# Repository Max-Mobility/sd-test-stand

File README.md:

# sd-test-stand
Test stand display, control, measurement, and validation code.

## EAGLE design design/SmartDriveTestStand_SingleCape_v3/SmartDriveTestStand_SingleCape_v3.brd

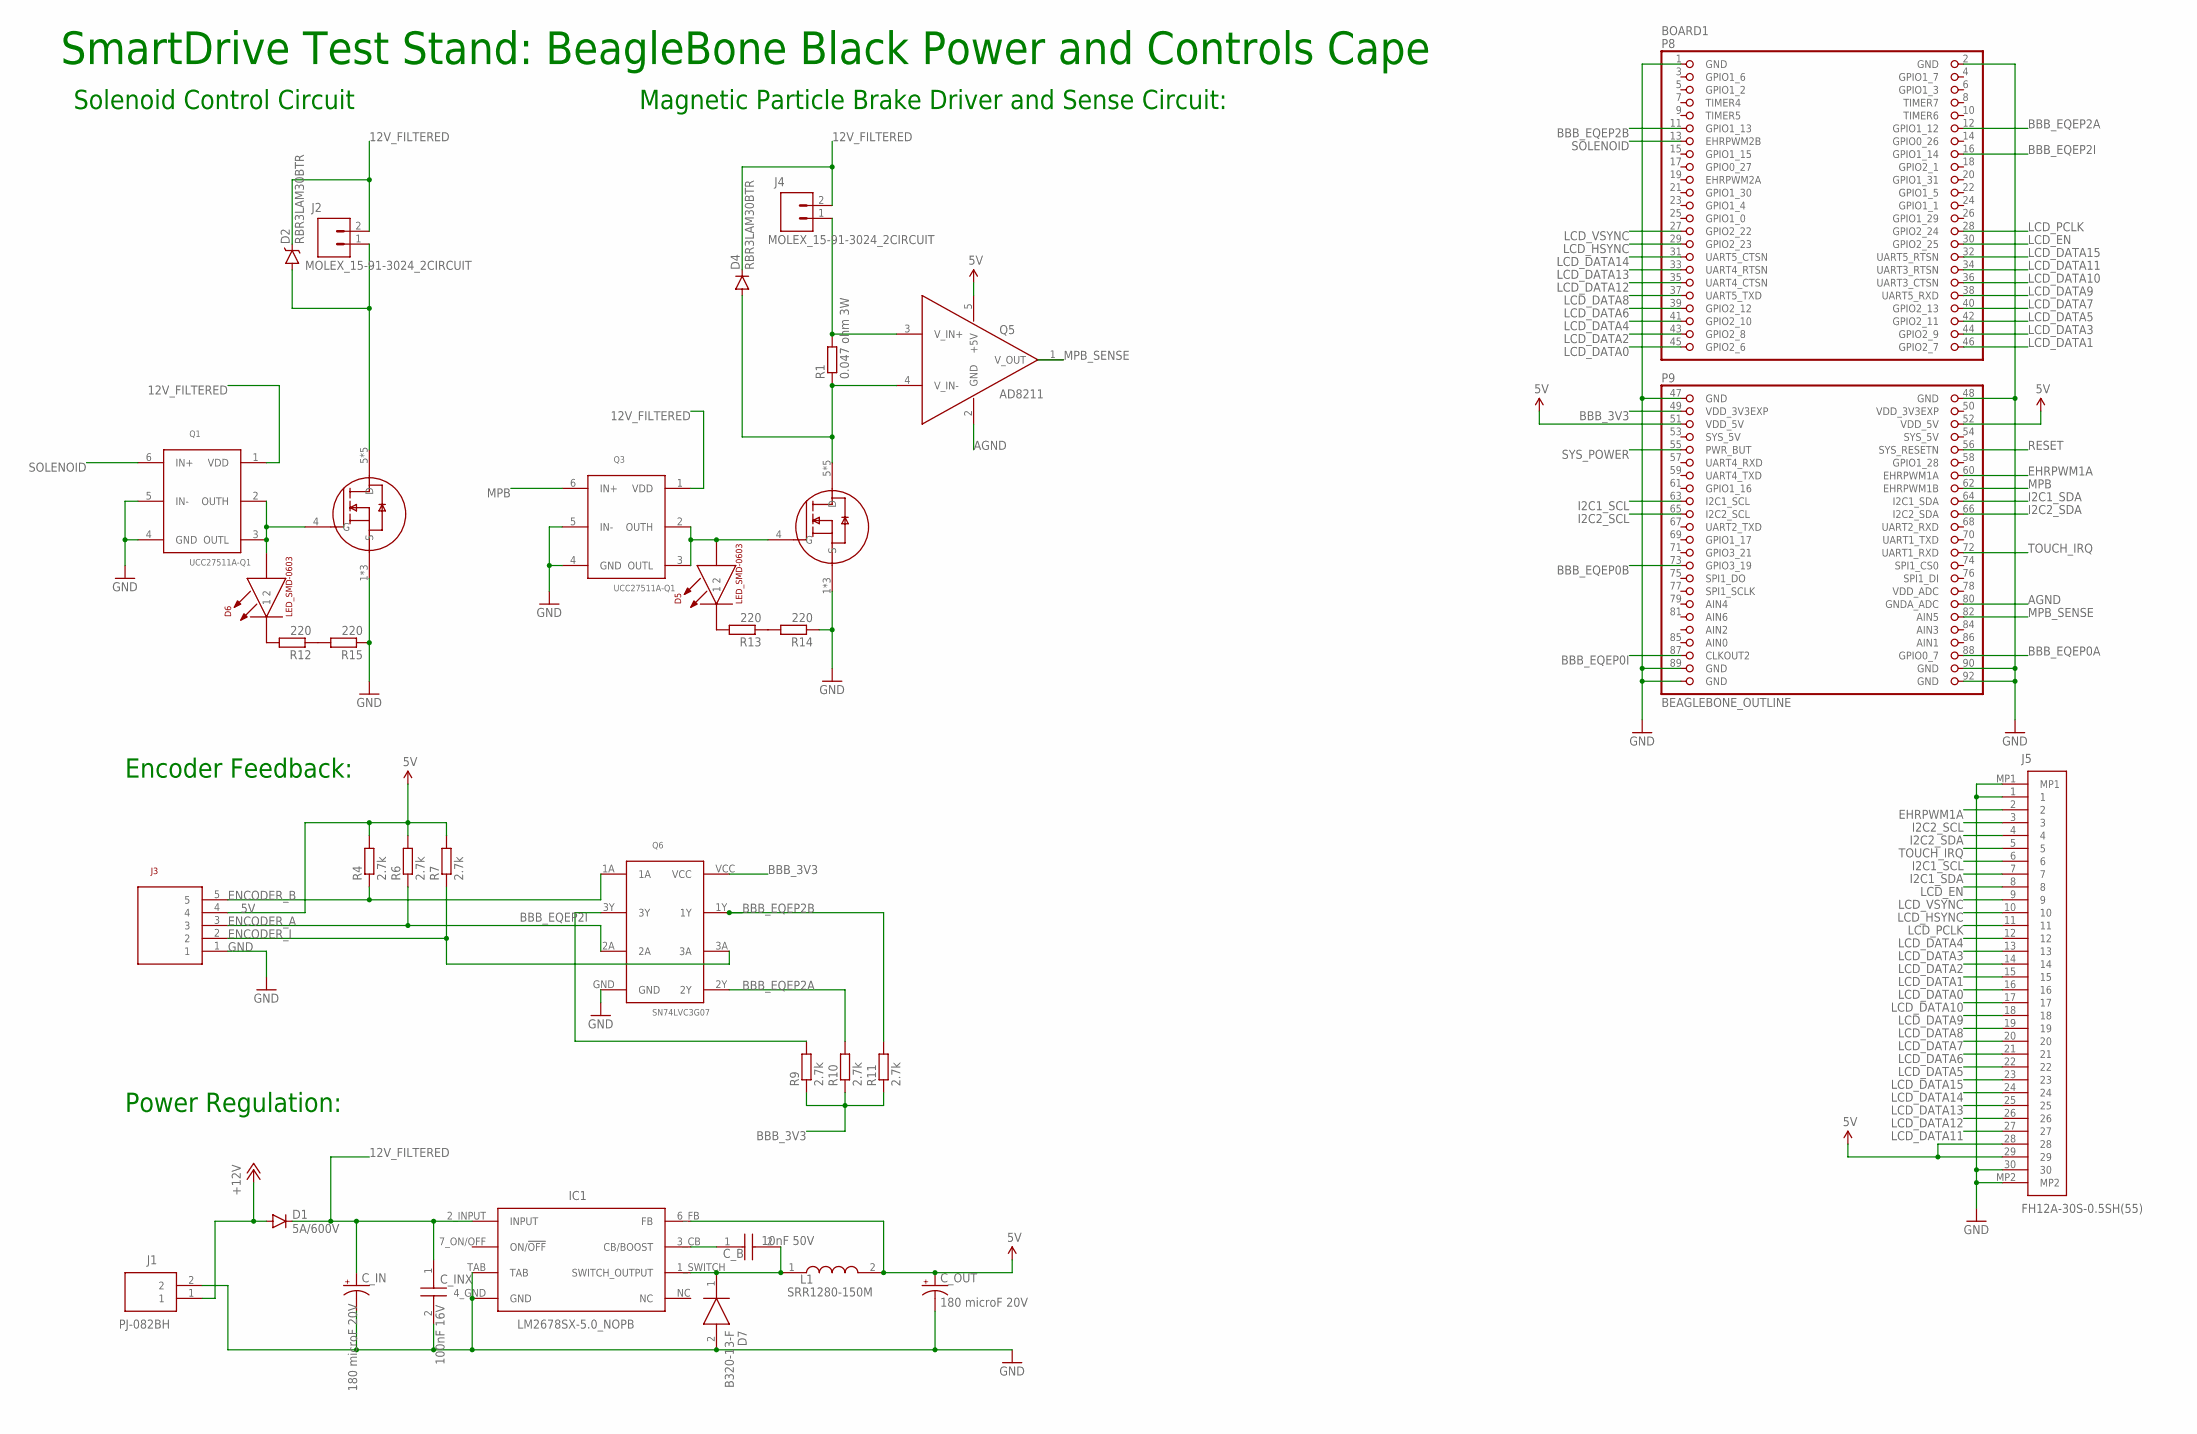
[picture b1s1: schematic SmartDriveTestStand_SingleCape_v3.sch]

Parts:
BOARD1: BEAGLEBONE_OUTLINE; BEAGLEBONE_SHIELD
C_B: 10nF 50V; CAPC2012X75N
C_IN: 180 microF 20V; CAPAE1030X800N
C_INX: 100nF 16V; CAPC1608X90N
C_OUT: 180 microF 20V; CAPAE1030X800N
D1: 5A/600V; SMC
D2, D4: RBR3LAM30BTR; SMA-DIODE
D5, D6: LED_SMD-0603; 0603_LED
D7: B320-13-F; DIOM7959X250N
IC1: LM2678SX-5.0_NOPB; KTW0007B
J1: PJ-082BH
J2, J4: MOLEX_15-91-3024_2CIRCUIT; MOLEX15-91-3024_2CIRCUIT
J3: MOLEX_15-91-3053_5CIRCUIT; MOLEX15-91-3053-5CIRCUIT
J5: FH12A-30S-0.5SH(55); FH12A30S05SH55
L1: SRR1280-150M
Q1, Q3: UCC27511A-Q1; SOT23-6
Q2, Q4: MOSFET_NCHANNELTI_CSD18533Q5A; SON_5X6MM_NEXFET
Q5: AD8211; SOT23-5
Q6: SN74LVC3G07
R1: 0.047 ohm 3W; RESISTOR-2512
R4, R6, R7, R9, R10, R11: 2.7k; RESISTOR-0603
R12, R13, R14, R15: 220; RESISTOR-0603

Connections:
5V: BOARD1.51 (VDD_5V), BOARD1.52 (VDD_5V), C_OUT.1 (+), IC1.6_FB (FB), J3.4, J5.28, J5.29, L1.2, Q5.5 (+5V), R4.P$2 (2), R6.P$2 (2), R7.P$2 (2)
12V_FILTERED: C_IN.1 (+), C_INX.1, D1.C, D2.C, D4.C, IC1.2_INPUT (INPUT), J2.2, J4.2, Q1.1 (VDD), Q3.1 (VDD)
+12V: D1.A, J1.1
AGND: BOARD1.80 (GNDA_ADC), Q5.2 (GND)
AIN0: BOARD1.85 (AIN0)
BBB_3V3: BOARD1.49 (VDD_3V3EXP), Q6.VCC, R9.P$1 (1), R10.P$1 (1), R11.P$1 (1)
BBB_EQEP0A: BOARD1.88 (GPIO0_7)
BBB_EQEP0B: BOARD1.73 (GPIO3_19)
BBB_EQEP0I: BOARD1.87 (CLKOUT2)
BBB_EQEP2A: BOARD1.12 (GPIO1_12), Q6.2Y, R10.P$2 (2)
BBB_EQEP2B: BOARD1.11 (GPIO1_13), Q6.1Y, R11.P$2 (2)
BBB_EQEP2I: BOARD1.16 (GPIO1_14), Q6.3Y, R9.P$2 (2)
EHRPWM1A: BOARD1.60 (EHRPWM1A), J5.2
ENCODER_A: J3.3, Q6.2A, R6.P$1 (1)
ENCODER_B: J3.5, Q6.1A, R4.P$1 (1)
ENCODER_I: J3.2, Q6.3A, R7.P$1 (1)
GND: BOARD1.1 (GND), BOARD1.2 (GND), BOARD1.47 (GND), BOARD1.48 (GND), BOARD1.89 (GND), BOARD1.90 (GND), BOARD1.91 (GND), BOARD1.92 (GND), C_IN.2 (-), C_INX.2, C_OUT.2 (-), D7.2 (A), IC1.4_GND (GND), IC1.TAB, J1.2, J3.1, J5.1, J5.30, J5.MP1, J5.MP2, Q1.4 (GND), Q1.5 (IN-), Q2.1 (S), Q2.2 (S), Q2.3 (S), Q3.4 (GND), Q3.5 (IN-), Q4.1 (S), Q4.2 (S), Q4.3 (S), Q6.GND, R14.P$1 (1), R15.P$1 (1)
I2C1_SCL: BOARD1.63 (I2C1_SCL), J5.6
I2C1_SDA: BOARD1.64 (I2C1_SDA), J5.7
I2C2_SCL: BOARD1.65 (I2C2_SCL), J5.3
I2C2_SDA: BOARD1.66 (I2C2_SDA), J5.4
LCD_DATA0: BOARD1.45 (GPIO2_6), J5.16
LCD_DATA1: BOARD1.46 (GPIO2_7), J5.15
LCD_DATA2: BOARD1.43 (GPIO2_8), J5.14
LCD_DATA3: BOARD1.44 (GPIO2_9), J5.13
LCD_DATA4: BOARD1.41 (GPIO2_10), J5.12
LCD_DATA5: BOARD1.42 (GPIO2_11), J5.22
LCD_DATA6: BOARD1.39 (GPIO2_12), J5.21
LCD_DATA7: BOARD1.40 (GPIO2_13), J5.20
LCD_DATA8: BOARD1.37 (UART5_TXD), J5.19
LCD_DATA9: BOARD1.38 (UART5_RXD), J5.18
LCD_DATA10: BOARD1.36 (UART3_CTSN), J5.17
LCD_DATA11: BOARD1.34 (UART3_RTSN), J5.27
LCD_DATA12: BOARD1.35 (UART4_CTSN), J5.26
LCD_DATA13: BOARD1.33 (UART4_RTSN), J5.25
LCD_DATA14: BOARD1.31 (UART5_CTSN), J5.24
LCD_DATA15: BOARD1.32 (UART5_RTSN), J5.23
LCD_EN: BOARD1.30 (GPIO2_25), J5.8
LCD_HSYNC: BOARD1.29 (GPIO2_23), J5.10
LCD_PCLK: BOARD1.28 (GPIO2_24), J5.11
LCD_VSYNC: BOARD1.27 (GPIO2_22), J5.9
MPB: BOARD1.62 (EHRPWM1B), Q3.6 (IN+)
MPB_SENSE: BOARD1.82 (AIN5), Q5.1 (V_OUT)
unnamed: R13.P$1 (1), R14.P$2 (2)
unnamed: D4.A, Q4.5 (D), Q4.6 (D), Q4.7 (D), Q4.8 (D), Q4.PAD (D), Q5.4 (V_IN-), R1.1
unnamed: D5.C (1), R13.P$2 (2)
unnamed: D6.C (1), R12.P$2 (2)
unnamed: D2.A, J2.1, Q2.5 (D), Q2.6 (D), Q2.7 (D), Q2.8 (D), Q2.PAD (D)
unnamed: J4.1, Q5.3 (V_IN+), R1.2
unnamed: R12.P$1 (1), R15.P$2 (2)
unnamed: D5.A (2), Q3.2 (OUTH), Q3.3 (OUTL), Q4.4 (G)
unnamed: D6.A (2), Q1.2 (OUTH), Q1.3 (OUTL), Q2.4 (G)
unnamed: C_B.2, D7.1 (K), IC1.1_SWITCH (SWITCH_OUTPUT), L1.1
unnamed: C_B.1, IC1.3_CB (CB/BOOST)
RESET: BOARD1.56 (SYS_RESETN)
SOLENOID: BOARD1.13 (EHRPWM2B), Q1.6 (IN+)
SYS_5V: BOARD1.53 (SYS_5V)
SYS_POWER: BOARD1.55 (PWR_BUT)
TOUCH_IRQ: BOARD1.72 (UART1_RXD), J5.5
VDD_3V3EXP: BOARD1.50 (VDD_3V3EXP)

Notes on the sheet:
SmartDrive Test Stand: BeagleBone Black Power and Controls Cape
Power Regulation:
Magnetic Particle Brake Driver and Sense Circuit:
Encoder Feedback:
Solenoid Control Circuit

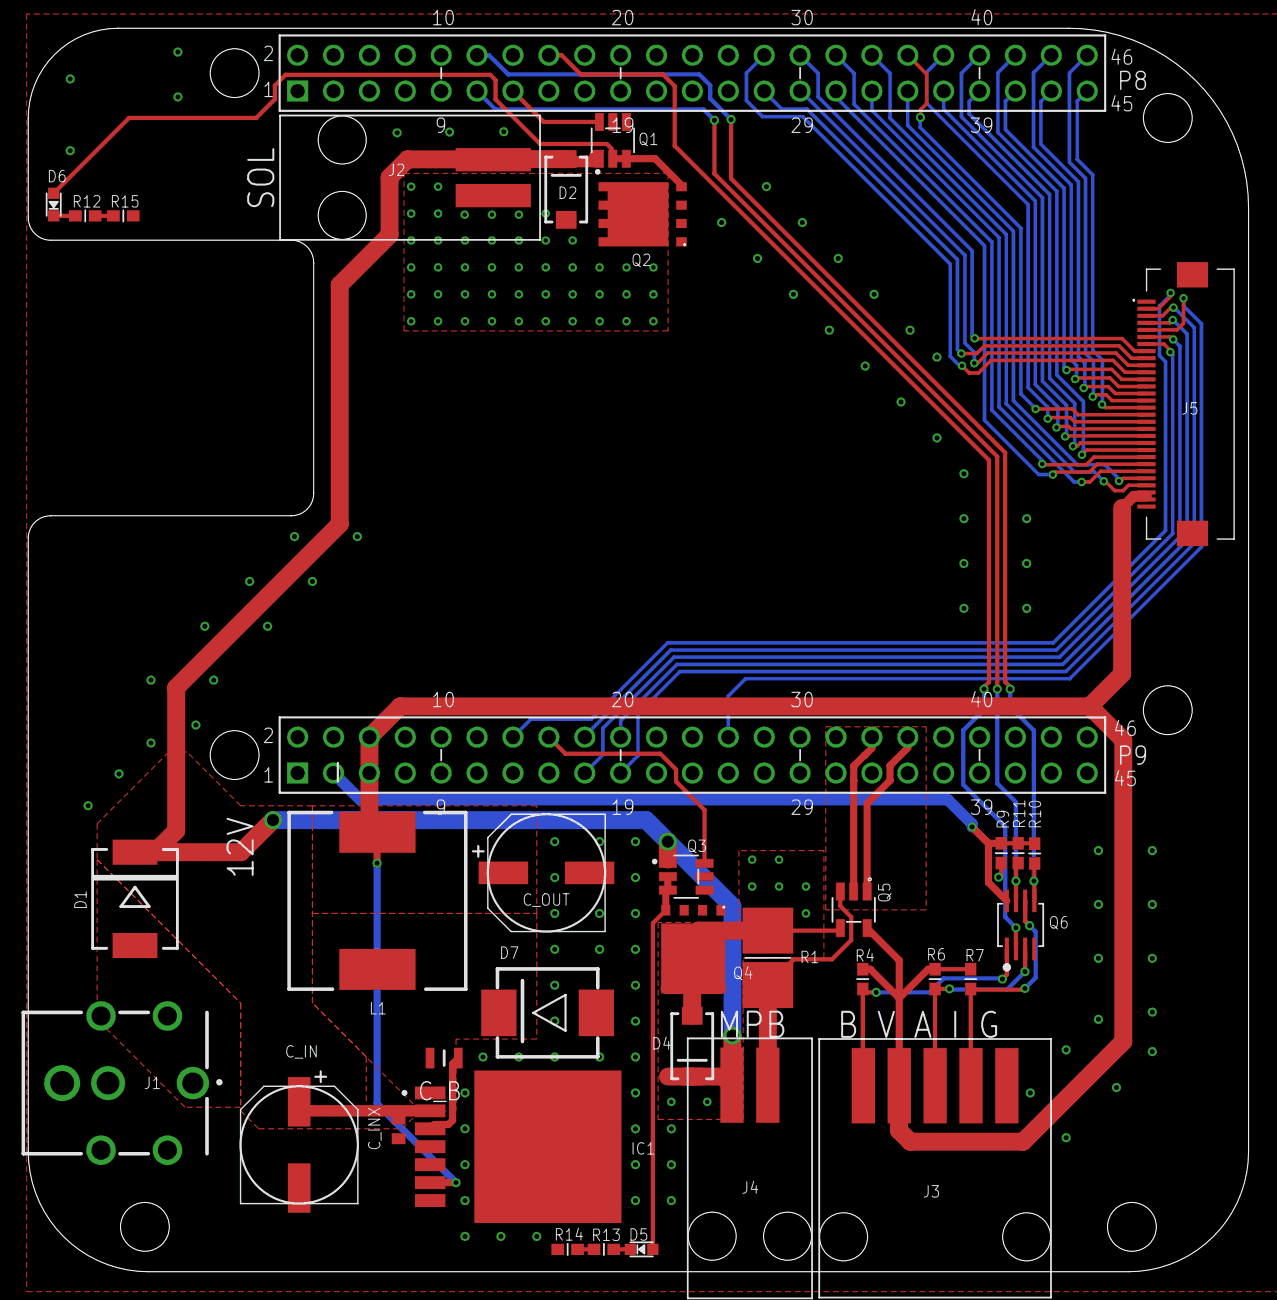
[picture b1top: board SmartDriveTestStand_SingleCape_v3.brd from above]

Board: 2 copper layers, 86.4 x 88.0 mm, 36 parts (0 on the bottom side), 52 nets.

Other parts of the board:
DRILEGEND: DRILEGEND

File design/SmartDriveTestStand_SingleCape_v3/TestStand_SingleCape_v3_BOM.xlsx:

Part | Value | Description | Quantity on Board | Package | Mouser Link | Alternate Part Link | Min Quantity | Current Stock | Ordered | MANUFACTURER_PART_NUMBER | MOUSER_PART_NUMBER
C_B | 10nF 50V | TDK 2012 CGA 10nF Ceramic Multilayer Capacitor, 50 V dc, +125C, C0G Dielectric,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 | 1 | CAPC2012X75N | https://www.mouser.com/ProductDetail/810-CGA4C2C0G1H103J | https://www.mouser.com/ProductDetail/TDK/C2012C0G1H103J060AA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 | 5 | 18 |  | CGA4C2C0G1H103J060AA | 810-CGA4C2C0G1H103J
C_IN, C_OUT | 180 microF 20V | Panasonic 180F 20 V dc Polymer Aluminium Electrolytic Capacitor E7, OS-CON Seri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 | 2 | CAPAE1030X800N |  |  | 10 | 16 |  | 20SVPF180M | 667-20SVPF180M
C_INX | 100nF 16V | KEMET 100nF Multilayer Ceramic Capacitor MLCC 16V dc 10% X7R Dielectric 0603 (1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 | 1 | CAPC1608X90N |  |  | 5 | 18 |  | C0603X104K4RACTU | 80-C0603X104K4R
C3 | 10uf,10V | Multilayer ceramic capacitor | 1 | CAPACITOR-1206 | https://www.mouser.com/ProductDetail/603-CC126ZRY5V6BB106 |  | 5 | 20 |  | CC1206ZRY5V6BB106
D1 | VS-5ECH06-M3/9AT | Rectifiers 5 Amp 600 Volts Hyperfast - Low QRR | 1 | SMC | https://www.mouser.com/ProductDetail/Vishay-Semiconductors/V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 | https://www.mouser.com/ProductDetail/Vishay-Semiconductors/V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 | 5 | 10 |  | VS-5ECH06-M3/9AT
D2, D4 | RBR3LAM30BTR | Schottky Diode 3A/30V | 2 | SMA-DIODE | https://www.mouser.com/ProductDetail/755-RBR3LAM30BTR |  | 10 | 15
D5, D6 | LED_SMD-0603 | Standard LEDs - SMD WL-SMCW SMDMono TpVw Waterclr 0603 Blue | 2 | SMD 0603 | https://www.mouser.com/ProductDetail/710-150060BS75000 |  | 10 | 21
D7 | B320-13-F | Diodes Inc B320-13-F, SMT Schottky Diode, 20V 3A, 2-Pin DO-214AB | 1 | DIOM7959X250N |  |  | 5 | 19 |  | B320-13-F | 621-B320-F
IC1 | LM2678SX-5.0_NOPB | SIMPLE SWITCHER 8V to 40V, 5A High Efficiency Step-Down DC/DC Switching Regulat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 | 1 | KTW0007B |  |  | 5 | 8 |  | LM2678SX-5.0/NOPB | 926-LM2678SX50NOPB
J1 | PJ-082BH | DC Power Connectors 2.5mm x 5.5mm horz | 1 |  | https://www.mouser.com/ProductDetail/CUI/PJ-082BH?qs=%2fha2p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 |  | 5 | 10 |  | PJ-082BH | 490-PJ-082BH
J2, J4 | MOLEX_15-91-3024_2POSITION | Molex Header, 2 position, with locking shroud | 2 | MOLEX15-91-3024_2POSITION | https://www.mouser.com/ProductDetail/538-15-91-3024 |  | 10 | 19 |  | 15-91-3024
J3 | MOLEX_15-91-3053_5POSITION | Molex Header, 5 position, with locking shroud | 1 | MOLEX15-91-3053_5POSITION | https://www.mouser.com/ProductDetail/538-15-91-3053 |  | 5 | 10 |  | 15-91-3053
J5 | FH12A-30S-0.5SH(55) | FFC & FPC Connectors 0.5MM 30 POS R/A TOP SMT GLD | 1 |  | https://www.mouser.com/ProductDetail/798-FH12A-30S0.5SH55 | https://www.mouser.com/ProductDetail/538-54104-3031 | 5 | 21 |  | FH12A-30S-0.5SH(55)
L1 | SRR1280-150M | Power inductor SMD shielded 15uH Bourns SRR1280 Series Shielded Wire-wound SMD 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 | 1 | SRR1280-150M |  |  | 5 | 8 |  | SRR1280-150M | 652-SRR1280-150M
Q1, Q3 | UCC27511A-Q1 | Gate Drivers Sngl-Ch high-Spd Low-Side Gate Driver | 2 | SOT23-6 | https://www.mouser.com/ProductDetail/595-UCC27511AQDBVRQ1 |  | 10 | 19 |  | UCC27511AQDBVRQ1
Q2, Q4 | MOSFET_NCHANNELTI_CSD18533Q5A | MOSFET 60V N-Chnl NexFET Pwr MSFT, CSD18533Q5 | 2 | SON_5X6MM_NEXFET | https://www.mouser.com/ProductDetail/595-CSD18533Q5A |  | 10 | 20 |  | CSD18533Q5A
Q5 | AD8211YRJZ-RL7 | Current Sense Amplifiers IC High VTG | 1 | SOT23-6 | https://www.mouser.com/ProductDetail/595-OPA365AQDBVRQ1 |  |  |  |  | AD8211YRJZ-RL7 | 584-AD8211YRJZ-R7
Q6 | SN74LVC3G07 | Buffers & Line Drivers Triple Buffer/Driver With Open-Drain Output 8-SM8 -40 to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 | 1 | SM-8 | https://www.mouser.com/ProductDetail/595-SN74LVC3G07DCT3 |  | 5 | 8 | 5 | SN74LVC3G07DCT3
R1 | 0.047ohm 1%, 3W | Current Sense Resistor GMR100HTBFQR047 | 1 | RESISTOR-2512 | https://www.mouser.com/ProductDetail/755-GMR100HTCFAR100 |  | 5 | 7 | 5 | GMR100HTBFQR047 | 755-GMR100HTBFQR047
R12, R13, R14, R15 | 220 Ohm 1/10W | Thin Film Resistors - SMD 1/10W 220 ohm 1% 50ppm | 4 | RESISTOR-0603 | https://www.mouser.com/ProductDetail/Yageo/RT0603FRE07220RL?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 |  | 20 | 92
R4, R6, R7, R9, R10, R11 | 2.7k 5%, 1/10W | Resistor 2.7k 5% | 6 | RESISTOR-0603 | https://www.mouser.com/ProductDetail/603-AC0603JR-072K7L |  | 30 | 121 |  | AC0603JR-072K7L
 |  |  |  |  |  |  | 0
Stackable Header | PRT-12790 | SparkFun Accessories Stackable Header 2x23 Pin Female | 2 |  | https://www.mouser.com/ProductDetail/474-PRT-12790 |  | 10 | 8 |  | PRT-12790
Receptacle Housing | 50-57-9405 | Headers & Wire Housings HSG 5P SINGLE ROW POSITIVE LATCH | 1 |  | https://www.mouser.com/ProductDetail/538-50-57-9405 |  | 5 | 10
Receptacle Housing | 50-57-9402 | Headers & Wire Housings HSG 2P SINGLE ROW POSITIVE LATCH | 2 |  | https://www.mouser.com/ProductDetail/538-50-57-9402 |  | 10 | 15

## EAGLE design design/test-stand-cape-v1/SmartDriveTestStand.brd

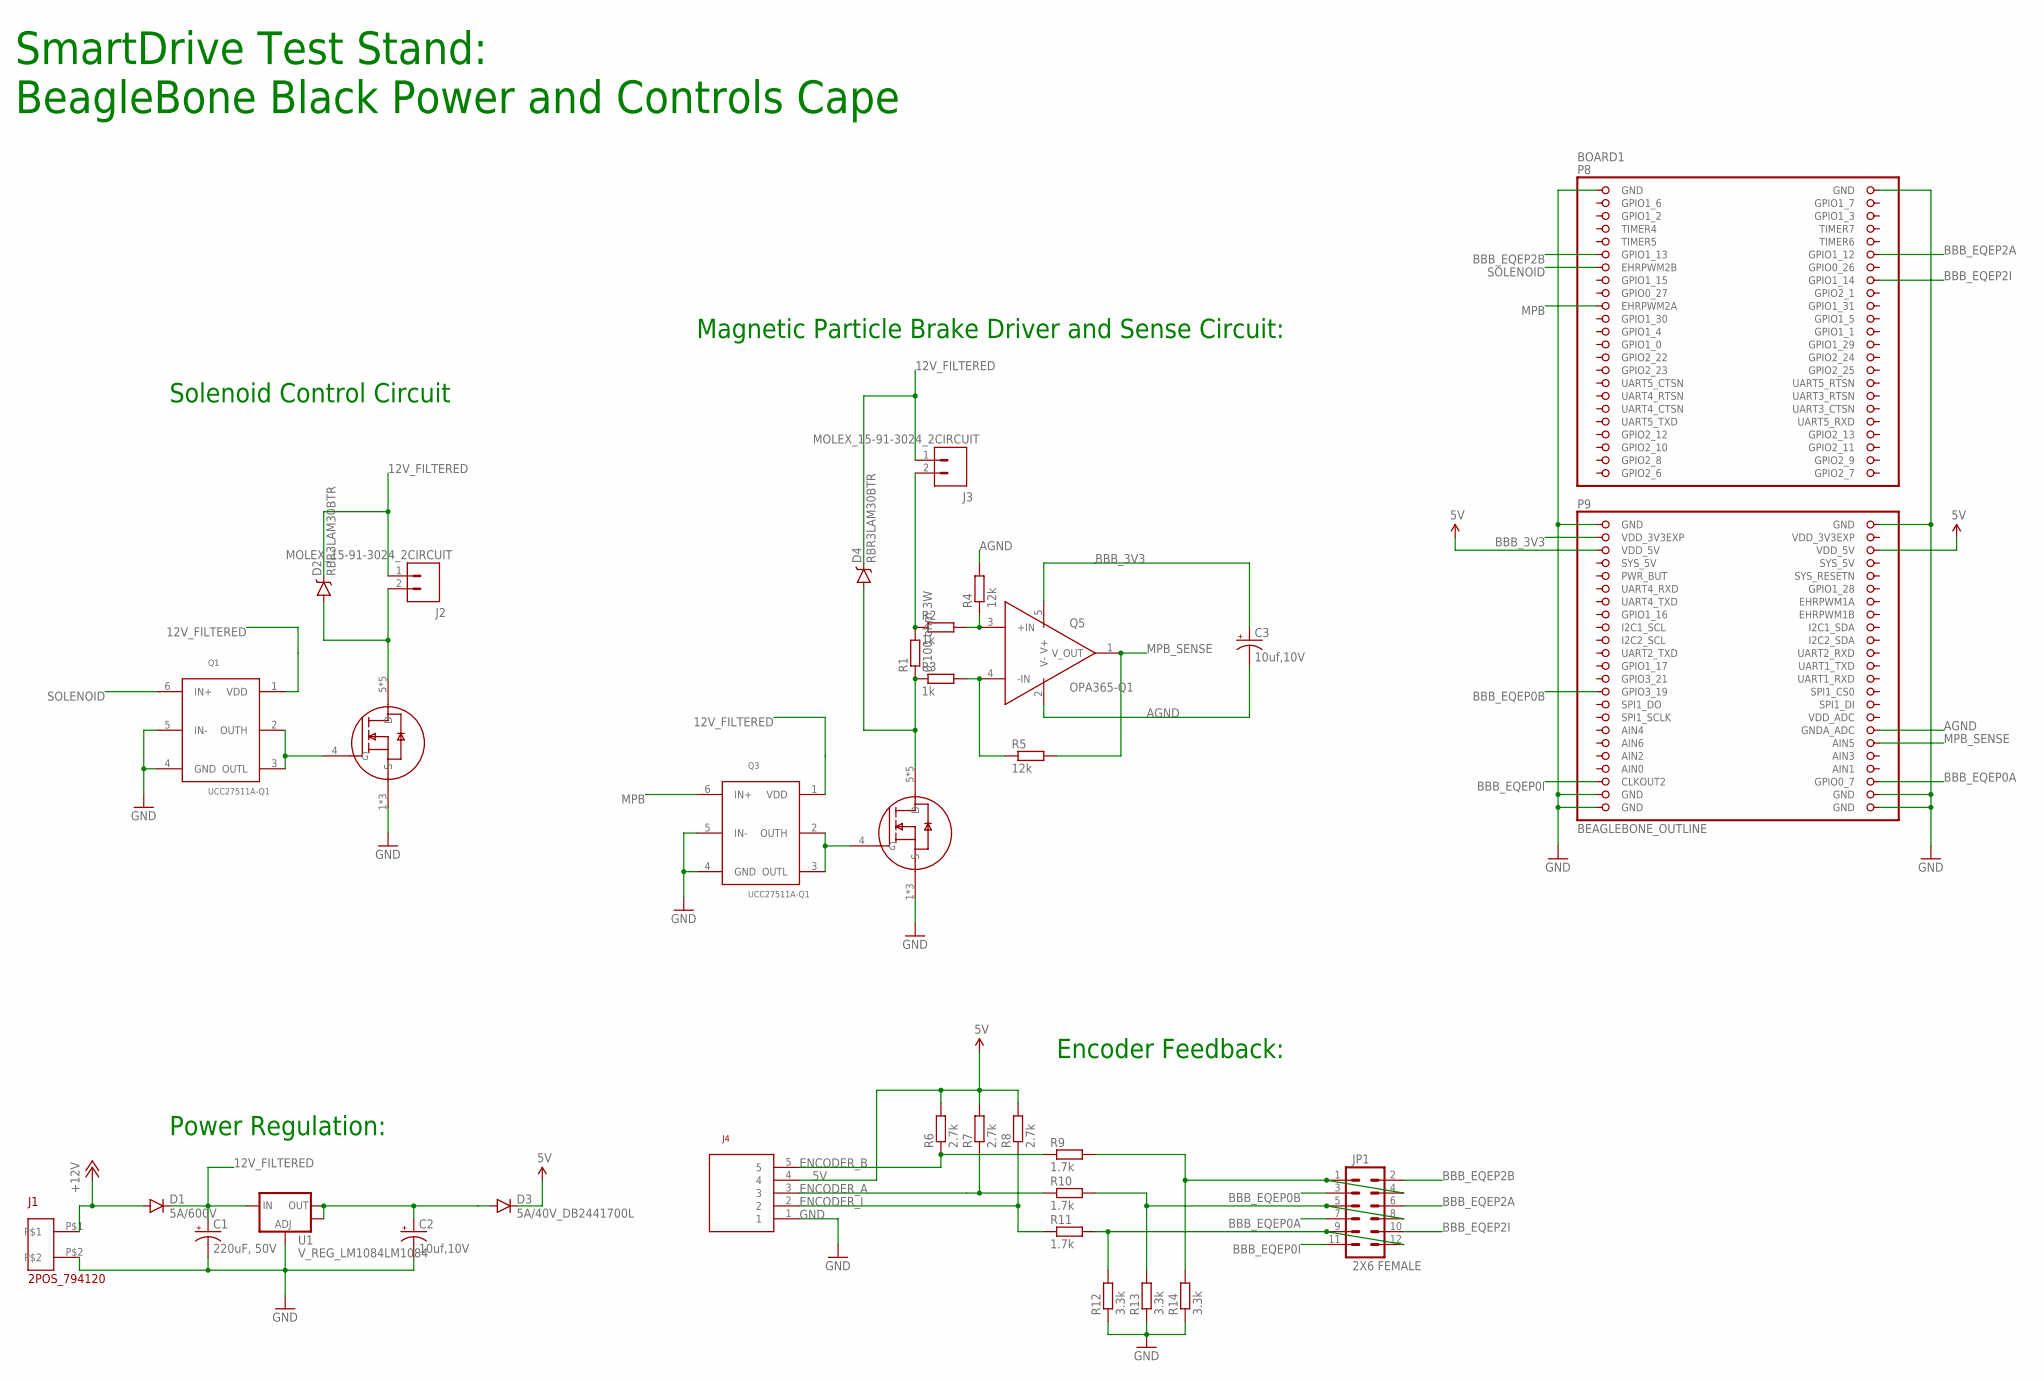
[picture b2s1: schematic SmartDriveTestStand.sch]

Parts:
BOARD1: BEAGLEBONE_OUTLINE; BEAGLEBONE_SHIELD
C1: 220uF, 50V; PANASONIC_G
C2, C3: 10uf,10V; EIA3216
D1: 5A/600V; SMC
D2, D4: RBR3LAM30BTR; SMA-DIODE
D3: 5A/40V_DB2441700L; SMA-DIODE_ALT
J1: 2POS_794120; 2POS_794120-1
J2, J3: MOLEX_15-91-3024_2CIRCUIT; MOLEX15-91-3024_2CIRCUIT
J4: MOLEX_15-91-3053_5CIRCUIT; MOLEX15-91-3053-5CIRCUIT
JP1: 2X6 FEMALE; 2X6
Q1, Q3: UCC27511A-Q1; SOT23-6
Q2, Q4: MOSFET_NCHANNELTI_CSD18533Q5A; SON_5X6MM_NEXFET
Q5: OPA365-Q1; SOT23-5
R1: 0.100 ohm 3W; RESISTOR-2512
R2, R3: 1k; RESISTOR-0603
R4, R5: 12k; RESISTOR-0603
R6, R7, R8: 2.7k; RESISTOR-0603
R9, R10, R11: 1.7k; RESISTOR-0603
R12, R13, R14: 3.3k; RESISTOR-0603
U1: V_REG_LM1084LM1084; TO-263-3

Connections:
5V: BOARD1.51 (VDD_5V), BOARD1.52 (VDD_5V), D3.C, J4.4, R6.P$2 (2), R7.P$2 (2), R8.P$2 (2)
12V_FILTERED: C1.+, D1.C, D2.C, D4.C, J2.1, J3.1, Q1.1 (VDD), Q3.1 (VDD), U1.3 (IN)
+12V: D1.A, J1.P$1
AGND: BOARD1.80 (GNDA_ADC), C3.C (-), Q5.2 (V-), R4.P$2 (2)
AIN0: BOARD1.85 (AIN0)
BBB_3V3: BOARD1.49 (VDD_3V3EXP), C3.A (+), Q5.5 (V+)
BBB_EQEP0A: BOARD1.88 (GPIO0_7), JP1.7
BBB_EQEP0B: BOARD1.73 (GPIO3_19), JP1.3
BBB_EQEP0I: BOARD1.87 (CLKOUT2), JP1.11
BBB_EQEP2A: BOARD1.12 (GPIO1_12), JP1.6
BBB_EQEP2B: BOARD1.11 (GPIO1_13), JP1.2
BBB_EQEP2I: BOARD1.16 (GPIO1_14), JP1.10
ENCA_1V8: JP1.5, JP1.8, R10.P$2 (2), R13.P$2 (2)
ENCB_1V8: JP1.1, JP1.4, R9.P$2 (2), R14.P$2 (2)
ENCI_1V8: JP1.9, JP1.12, R11.P$2 (2), R12.P$2 (2)
ENCODER_A: J4.3, R7.P$1 (1), R10.P$1 (1)
ENCODER_B: J4.5, R6.P$1 (1), R9.P$1 (1)
ENCODER_I: J4.2, R8.P$1 (1), R11.P$1 (1)
GND: BOARD1.1 (GND), BOARD1.2 (GND), BOARD1.47 (GND), BOARD1.48 (GND), BOARD1.89 (GND), BOARD1.90 (GND), BOARD1.91 (GND), BOARD1.92 (GND), C1.-, C2.C (-), J1.P$2, J4.1, Q1.4 (GND), Q1.5 (IN-), Q2.1 (S), Q2.2 (S), Q2.3 (S), Q3.4 (GND), Q3.5 (IN-), Q4.1 (S), Q4.2 (S), Q4.3 (S), R12.P$1 (1), R13.P$1 (1), R14.P$1 (1), U1.1 (ADJ)
MPB: BOARD1.19 (EHRPWM2A), Q3.6 (IN+)
MPB_SENSE: BOARD1.82 (AIN5), Q5.1 (V_OUT), R5.P$2 (2)
unnamed: Q3.2 (OUTH), Q3.3 (OUTL), Q4.4 (G)
unnamed: D4.A, Q4.5 (D), Q4.6 (D), Q4.7 (D), Q4.8 (D), Q4.PAD (D), R1.1, R3.P$1 (1)
unnamed: Q5.3 (+IN), R2.P$2 (2), R4.P$1 (1)
unnamed: Q5.4 (-IN), R3.P$2 (2), R5.P$1 (1)
unnamed: Q1.2 (OUTH), Q1.3 (OUTL), Q2.4 (G)
unnamed: D2.A, J2.2, Q2.5 (D), Q2.6 (D), Q2.7 (D), Q2.8 (D), Q2.PAD (D)
unnamed: J3.2, R1.2, R2.P$1 (1)
SOLENOID: BOARD1.13 (EHRPWM2B), Q1.6 (IN+)
SYS_5V: BOARD1.53 (SYS_5V)
VDD_3V3EXP: BOARD1.50 (VDD_3V3EXP)
VOUT: C2.A (+), D3.A, U1.2 (OUT), U1.4 (OUT)

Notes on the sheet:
SmartDrive Test Stand: BeagleBone Black Power and Controls Cape
Power Regulation:
Magnetic Particle Brake Driver and Sense Circuit:
Encoder Feedback:
Solenoid Control Circuit

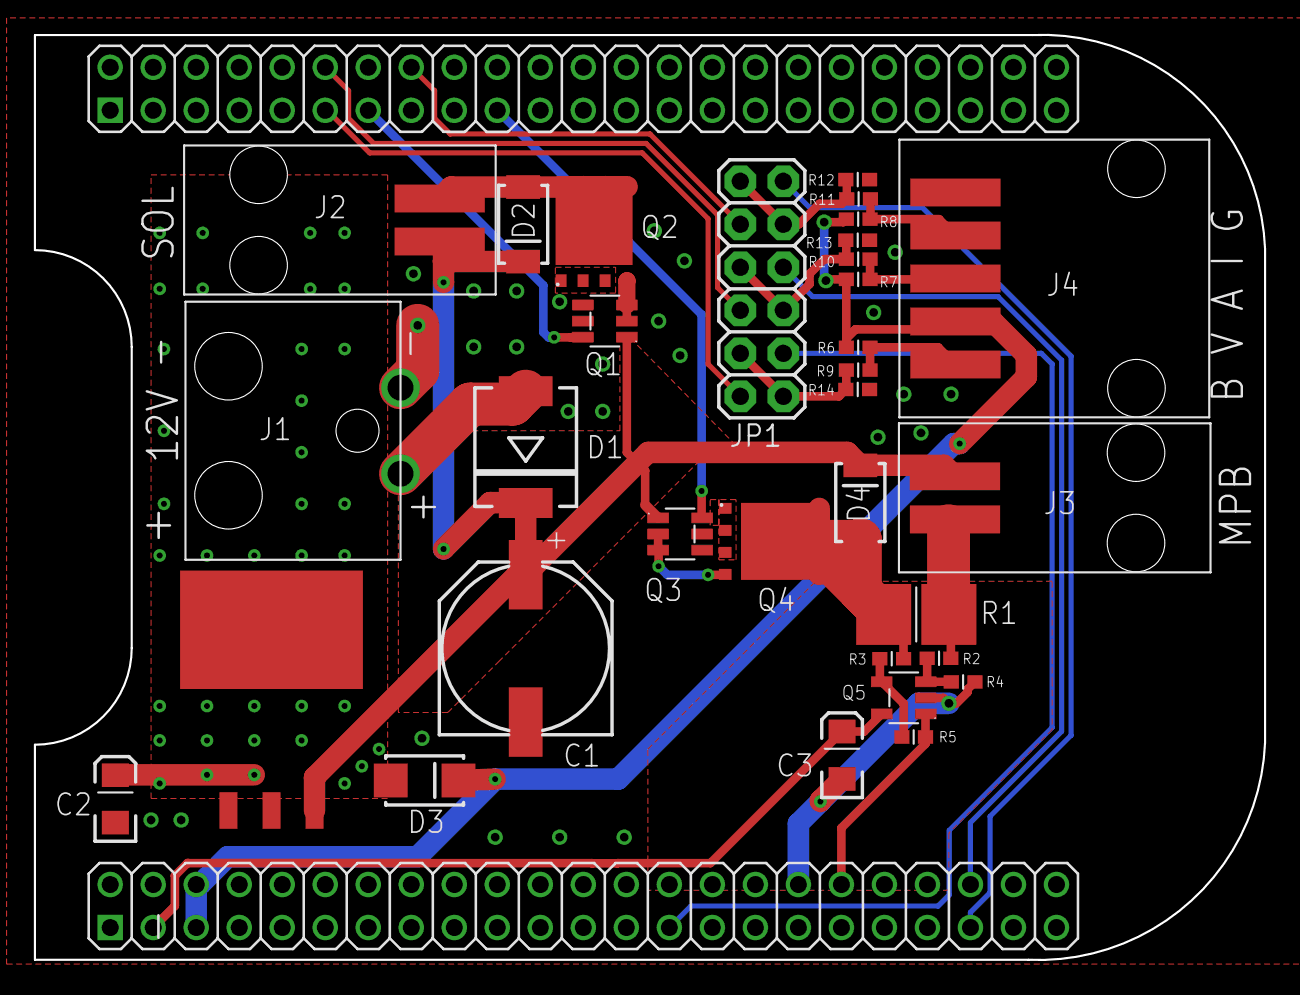
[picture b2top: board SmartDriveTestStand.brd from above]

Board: 2 copper layers, 72.6 x 54.6 mm, 34 parts (0 on the bottom side), 29 nets.

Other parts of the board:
DRILEGEND: DRILEGEND

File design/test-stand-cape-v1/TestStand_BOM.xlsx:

Part | Value | Description | Quantity on Board | Package | Mouser Link
2P Jumper | 929951-00 | Encoder Routing Jumper | 3 |  | https://www.mouser.com/ProductDetail/3M-Electronic-Solutions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
BOARD1 | BEAGLEBONE_OUTLINE |  |  | BEAGLEBONE_SHIELD
C1 | 220uF, 50V | Aluminum Electrolytic Capacitor, EEE-FK1H221P | 1 | PANASONIC_G | https://www.mouser.com/ProductDetail/667-EEE-FK1H221P
C2, C3 | 10uf,10V | Multilayer ceramic capacitor | 2 | CAPACITOR-1206 | https://www.mouser.com/ProductDetail/603-CC126ZRY5V6BB106
Contact - Socket | 16-02-0102 | Headers & Wire Housings 22-24 TERMINAL BULK FEMALE | 11 |  | https://www.mouser.com/ProductDetail/538-16-02-0102
D1 | VS-5ECH06-M3/9AT | Rectifiers 5 Amp 600 Volts Hyperfast - Low QRR | 1 | SMC | https://www.mouser.com/ProductDetail/Vishay-Semiconductors/V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
D2, D4 | RBR3LAM30BTR | Schottky Diode 3A/30V | 2 | SMA-DIODE | https://www.mouser.com/ProductDetail/755-RBR3LAM30BTR
D3 | 5A/40V_DB2441700L | Diodes - General Purpose, Power, Switching Schottky Barrier Diode | 1 | SMA-DIODE_ALT | https://www.mouser.com/ProductDetail/Panasonic/DB2441700L?qs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
J1, J2, J3 | MOLEX_15-91-3024_2POSITION | Molex Header, 2 position, with locking shroud | 3 | MOLEX15-91-3024_2POSITION | https://www.mouser.com/ProductDetail/538-15-91-3024
J4 | MOLEX_15-91-3053_5POSITION | Molex Header, 5 position, with locking shroud | 1 | MOLEX15-91-3053_5POSITION | https://www.mouser.com/ProductDetail/538-15-91-3053
JP1 | 929665-01-06-EU | Headers & Wire Housings 12P PIN STRIP HEADER STRAIGHT, GOLD, 2ROW | 1 | 2X6 | https://www.mouser.com/ProductDetail/3M-Electronic-Solutions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
Q1, Q3 | UCC27511A-Q1 | Gate Drivers Sngl-Ch high-Spd Low-Side Gate Driver | 2 | SOT23-6 | https://www.mouser.com/ProductDetail/595-UCC27511AQDBVRQ1
Q2, Q4 | MOSFET_NCHANNELTI_CSD18533Q5A | MOSFET 60V N-Chnl NexFET Pwr MSFT, CSD18533Q5 | 2 | SON_5X6MM_NEXFET | https://www.mouser.com/ProductDetail/595-CSD18533Q5A
Q5 | OPA365AQDBVRQ1 | TI Op-Amp OPA365AQDBVRQ1 | 1 | SOT23-5 | https://www.mouser.com/ProductDetail/595-OPA365AQDBVRQ1
R1 | 0.100ohm 1%, 3W | Current Sense Resistor GMR100HTCFAR100 | 1 | RESISTOR-2512 | https://www.mouser.com/ProductDetail/755-GMR100HTCFAR100
R12, R13, R14 | 3.3k 1%, 1/10W | Resistor 3.3kOhm 1%, 1/10W | 3 | RESISTOR-0603 | https://www.mouser.com/ProductDetail/Yageo/AC0603FR-073K3L?q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
R2, R3 | 1k 0.5%, 1/10W | Resistor 1k 0.5% | 2 | RESISTOR-0603 | https://www.mouser.com/ProductDetail/603-AT0603DRD071KL
R4, R5 | 12k 0.5%, 1/10W | Resistor 12kOhm 0.5%, 1/10W | 2 | RESISTOR-0603 | https://www.mouser.com/ProductDetail/Yageo/RT0603DRE0712KL?q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
R6, R7, R8 | 2.7k 5%, 1/10W | Resistor 2.7k 5% | 3 | RESISTOR-0603 | https://www.mouser.com/ProductDetail/603-AC0603JR-072K7L
R9, R10, R11 | 1.69k 1%, 1/10W | Resistor 1.69kOhm 1%, 1/10W | 3 | RESISTOR-0603 | https://www.mouser.com/ProductDetail/Yageo/AC0603FR-071K69L?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
Receptacle Housing | 50-57-9405 | Headers & Wire Housings HSG 5P SINGLE ROW POSITIVE LATCH | 1 |  | https://www.mouser.com/ProductDetail/538-50-57-9405
Receptacle Housing | 50-57-9402 | Headers & Wire Housings HSG 2P SINGLE ROW POSITIVE LATCH | 3 |  | https://www.mouser.com/ProductDetail/538-50-57-9402
U1 | V_REG_LM1084 | LDO Voltage Regulator, 5V Fixed, LM1084ISX-5.0/NOPB | 1 | TO-263-3 | https://www.mouser.com/ProductDetail/926-LM1084ISX50NOPB

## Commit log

2018-11-26 added uboot config file.
2018-11-27 Create design/test-stand-cape-v1/description
2018-11-27 Update description
2018-11-27 Create test-stand-cape_Single-Cape
2018-11-27 Rename design/test-stand-cape_Single-Cape/design to design/test-stand-cape_Single-Cape_v2/design
2018-11-27 Update design
2018-11-27 minor update.
2019-01-16 added code from sd-programmer.
2019-01-16 removing unneeded deps.
2019-01-16 bugfix.
2019-01-16 working execution on bbb.
2019-01-16 minor update to readme.
2019-01-16 added imports of adafruit_bbio
2019-01-16 WIP adding reading of encoder and control over PWM to ui code.
2019-01-16 cleanup PWM resources / shut off channels when closing.
2019-01-16 continuing to flesh out pin controls.
2019-01-17 removed unneeded env file. minor updates.
2019-01-17 working on fleshing out the ui for working event binding and data display.
2019-01-17 added zero load button and updated progress bar display.
2019-01-21 WIP adding encoder speed measurement / computation / display
2019-01-21 working speed display.

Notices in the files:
parts and their libraries:
SparkFun-Aesthetics: Licensing: CC v3.0 Share-Alike You are welcome to use this library for commercial purposes.
SparkFun-Connectors: Licensing: Creative Commons ShareAlike 4.0 International - https://creativecommons.org/licenses/by-sa/4.0
